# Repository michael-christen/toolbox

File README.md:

# toolbox

My personal monorepo — scripts, libraries, and applications built with Bazel
across Python, C++, and Rust.

**[Documentation](https://michael-christen.github.io/toolbox)** — architecture,
setup, language guides, and command references.

All project code lives under [`tlbox/`](tlbox/) — a language-agnostic namespace
for Python, C++, Rust, and hardware code alike. See
[`docs/development.md`](docs/development.md) to get started, or the
[docs site](https://michael-christen.github.io/toolbox) for everything else.

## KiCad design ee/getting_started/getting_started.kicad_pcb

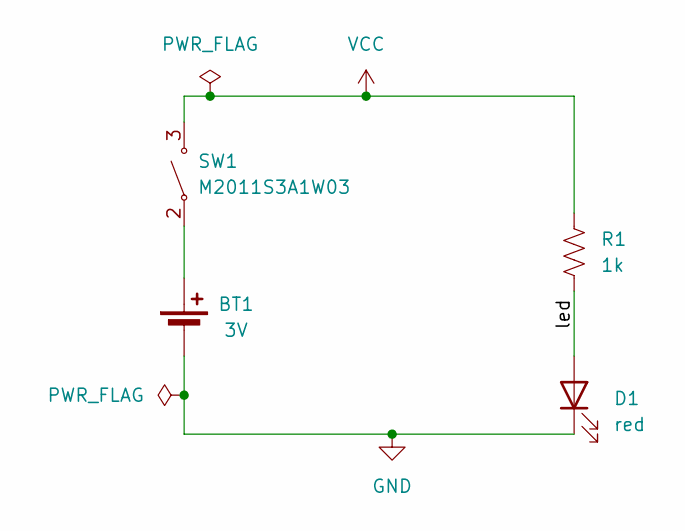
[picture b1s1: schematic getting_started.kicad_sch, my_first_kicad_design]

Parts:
BT1: 3V; BatteryHolder_Keystone_1058_1x2032
D1: red; LED_D5.0mm
R1: 1k; R_Axial_DIN0309_L9.0mm_D3.2mm_P12.70mm_Horizontal
SW1: M2011S3A1W03; Switch_Toggle_SPST_NKK_M2011S3A1x03

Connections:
/led: D1.2 (A), R1.1
GND: BT1.2 (-), D1.1 (K)
unnamed: BT1.1 (+), SW1.2 (A)
VCC: R1.2, SW1.3 (B)

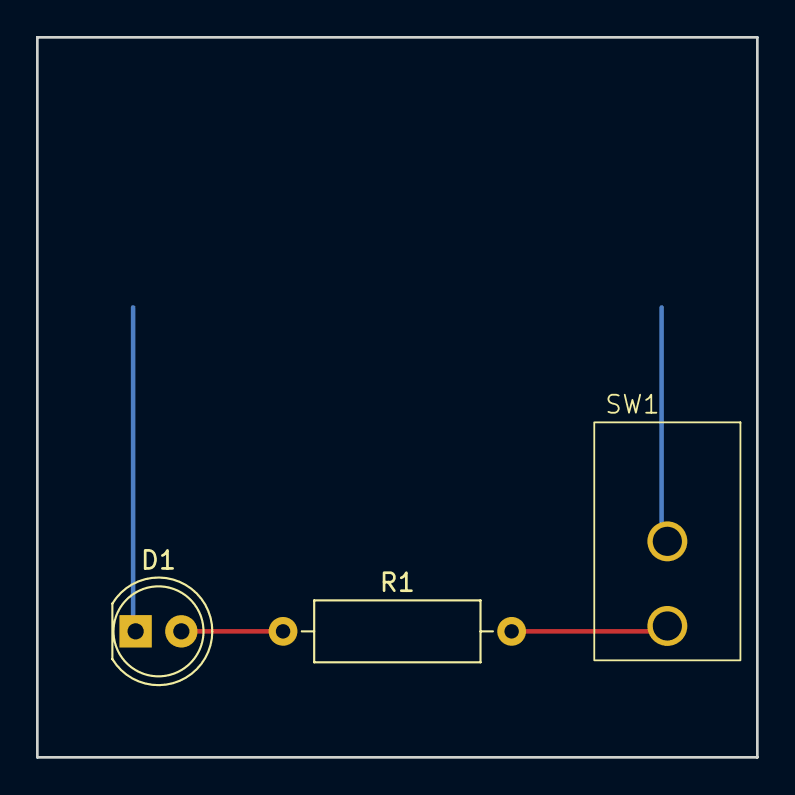
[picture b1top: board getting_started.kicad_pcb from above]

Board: 2 copper layers, 40.0 x 40.0 mm, 4 parts (1 on the bottom side), 4 nets.

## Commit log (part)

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2026-04-02 Fix autoapi by enabling symlink traversal (sphinx-autoapi 3.7.0)
    sphinx-autoapi 3.7.0 introduced autoapi_follow_symlinks with a default
    of False. Bazel sandboxes all source inputs as symlinks, so autoapi
    stopped finding Python files and produced empty API docs.
    https://claude.ai/code/session_01Bn39Pe4L2SSyeQ5M53nFwb
2026-04-02 Apply prettier formatting to markdown files
    https://claude.ai/code/session_013eKgR1WYFB6zvYaCg11DBT
2026-04-02 Fix mypy and query generator failures
    - Use googleapiclient.discovery.Resource type (correct), add
    # type: ignore[attr-defined] for dynamically-generated users() method
    - Add //apps/gmail_analysis:gmail_analysis to packaging/generated.bzl
    https://claude.ai/code/session_01RizaWooJZTLLvezf5z8nag
2026-04-02 Add git LFS documentation to development guide
    https://claude.ai/code/session_01W7Da8VTU6GixAC1fJchVH4
2026-04-03 Lint
2026-04-03 type support
2026-04-03 Bump pyopenssl from 18.0.0 to 26.0.0 in /tlbox/apps/csv-to-sheets
    Bumps [pyopenssl](https://github.com/pyca/pyopenssl) from 18.0.0 to 26.0.0.
    - [Changelog](https://github.com/pyca/pyopenssl/blob/main/CHANGELOG.rst)
    - [Commits](https://github.com/pyca/pyopenssl/compare/18.0.0...26.0.0)
    ---
    updated-dependencies:
    - dependency-name: pyopenssl
2026-04-03 Notes
2026-04-03 Move lint/build/test to BuildBuddy, keep coverage/metrics in GitHub
    BuildBuddy runs in ~1 min vs GitHub's ~10 min, so lint/build/test
    belong there. GitHub CI is now split into two jobs:
    - coverage_and_metrics (required check)
    - build_and_test (non-required, duplicates BuildBuddy for visibility)
    Note: update branch protection to require coverage_and_metrics instead
    of build_and_test.
2026-04-03 Fix missing libncurses5 in coverage_and_metrics job
    Coverage still builds C++ via the llvm toolchain, so libtinfo.so.5
    is still required even without the lint step.
    https://claude.ai/code/session_013eKgR1WYFB6zvYaCg11DBT
2026-04-03 Set permissions
2026-04-03 Bump cryptography from 43.0.1 to 46.0.6 in /tlbox/apps/csv-to-sheets
    Bumps [cryptography](https://github.com/pyca/cryptography) from 43.0.1 to 46.0.6.
    - [Changelog](https://github.com/pyca/cryptography/blob/main/CHANGELOG.rst)
    - [Commits](https://github.com/pyca/cryptography/compare/43.0.1...46.0.6)
    ---
    updated-dependencies:
    - dependency-name: cryptography
2026-04-03 Set these up for bazel
2026-04-03 Format
2026-04-03 Remove legacy apps with their own requirements (#289)
    ## Summary
    Dependabot keeps trying to adjust these, let's just opt into bazel
    - **Remove extra requirements**
    - **Set these up for bazel**
    <!-- What does this PR do and why? -->
    ## Test plan
2026-04-03 Bump pyasn1 from 0.6.2 to 0.6.3
    Bumps [pyasn1](https://github.com/pyasn1/pyasn1) from 0.6.2 to 0.6.3.
    - [Release notes](https://github.com/pyasn1/pyasn1/releases)
    - [Changelog](https://github.com/pyasn1/pyasn1/blob/main/CHANGES.rst)
    - [Commits](https://github.com/pyasn1/pyasn1/compare/v0.6.2...v0.6.3)
    ---
    updated-dependencies:
2026-04-03 Bump requests from 2.32.5 to 2.33.0
    Bumps [requests](https://github.com/psf/requests) from 2.32.5 to 2.33.0.
    - [Release notes](https://github.com/psf/requests/releases)
    - [Changelog](https://github.com/psf/requests/blob/main/HISTORY.md)
    - [Commits](https://github.com/psf/requests/compare/v2.32.5...v2.33.0)
    ---
    updated-dependencies:
2026-04-03 Bump black from 26.1.0 to 26.3.1
    Bumps [black](https://github.com/psf/black) from 26.1.0 to 26.3.1.
    - [Release notes](https://github.com/psf/black/releases)
    - [Changelog](https://github.com/psf/black/blob/main/CHANGES.md)
    - [Commits](https://github.com/psf/black/compare/26.1.0...26.3.1)
    ---
    updated-dependencies:
2026-04-03 Automatically Upgrade Dependencies
2026-04-03 Automatically Upgrade Dependencies (#297)
    Automatically Upgrade Dependencies - by upgrade-dependencies.yml
2026-04-03 Bump setuptools from 70.3.0 to 78.1.1
    Bumps [setuptools](https://github.com/pypa/setuptools) from 70.3.0 to 78.1.1.
    - [Release notes](https://github.com/pypa/setuptools/releases)
    - [Changelog](https://github.com/pypa/setuptools/blob/main/NEWS.rst)
    - [Commits](https://github.com/pypa/setuptools/compare/v70.3.0...v78.1.1)
    ---
    updated-dependencies:
2026-04-03 Adjust setuptools
2026-04-03 deploy: a6e39ded6b5a899a6d9c914769f78cbac9576afd
2026-04-03 Add to actions checkout
2026-04-03 Fix action
2026-04-03 fix actions
2026-04-03 Add trim branches script
2026-04-03 Move gmail analysis (#300)
    ## Summary
    On the tin
    <!-- What does this PR do and why? -->
    ## Test plan
    - CI
2026-04-05 Add lsm6dso and m2t550 drivers under tlbox/hw/drivers/
    Moves the new driver work into the new directory structure introduced
    in #256 (hw_drivers/ -> tlbox/hw/). Updates BUILD to use nanopb
    pattern matching lis3mdl, and fixes include paths throughout.
    Closes #157
    https://claude.ai/code/session_013eKgR1WYFB6zvYaCg11DBT
2026-04-05 Resolve all XXX comments in lsm6dso driver
    - Fix FuncCfgAccess bit positions (bits 6/7 per datasheet, not 0/1)
    - Replace example.cc/.h with a proper lsm6dso_pw_test.cc
    - Stub out sim_lsm6dso.cc with Unimplemented() pending full implementation
    - Remove speculative/WIP XXX comments from .emb and .proto
    - Add *.pdf to .gitattributes as LFS binary
    - Use git grep -I in lint.sh to skip binary files in XXX check
2026-04-06 wrench
2026-04-06 fix pointer
2026-04-06 Add beginning of lsm6dso and m2t550 drivers (#157)
    ## Summary
    - Adds LSM6DSO IMU driver (3-axis gyro + accelerometer) under
    `tlbox/hw/drivers/lsm6dso/`
    - Emboss register definitions (`.emb`)
    - Proto definitions for config/telemetry
    - BUILD updated to nanopb pattern matching `lis3mdl`
2026-04-06 Got an example vpython interaction:
    - robot block
    - viewable wheel rotation
    - reaction to keys pressed
    NEXT: move the robot, make a floor grid, change keypress
    Get all keys at once
    It's alive, just path, no torque
2026-04-06 More lint :(
2026-04-06 cleanup
2026-04-06 Create local vpython
2026-04-06 Update requirements
2026-04-06 Remove
2026-04-06 Enable remote_cache_compression
2026-04-06 Fix self-edge
2026-04-06 A bunch of raw notes after reading bazel docs (#80)
2026-04-07 Update aspect rules_py (#304)
    On the tin, see https://github.com/aspect-build/rules_py/pull/840
    Should bring in bin scripts, though didn't get evidence of that
2026-04-07 deploy: 5629891ece6f42bcb188f826ac68bae6bd585cb1
2026-04-07 update kicad v10
2026-04-07 Wild
2026-04-08 Say -y
2026-04-08 Bump cryptography from 46.0.6 to 46.0.7
    Bumps [cryptography](https://github.com/pyca/cryptography) from 46.0.6 to 46.0.7.
    - [Changelog](https://github.com/pyca/cryptography/blob/main/CHANGELOG.rst)
    - [Commits](https://github.com/pyca/cryptography/compare/46.0.6...46.0.7)
    ---
    updated-dependencies:
    - dependency-name: cryptography
2026-04-09 Design doc
2026-04-09 Add some dates
2026-04-11 Update gazelle
2026-04-13 New schematic
2026-04-13 Add links and fix after lint
2026-04-13 Revert "Defer KiCad Bazel rules and hardware docs to stacked PR"
    This reverts commit 9ad1201c066043e5dfe772eac2c05005862cd8ec.
2026-04-13 deploy: af9f19203feb895afe8c03bcc65f4dfa55a2b86a
2026-04-13 Fix #319: generate KiCad hardware artifacts in docs workflow
    - Add workflow_dispatch trigger with optional publish input so docs can
    be built and inspected without automatically pushing to GitHub Pages
    - Install kicad-cli (via KiCad 7 PPA) to generate PDFs from KiCad
    schematic and PCB files for sbr_pcb_v1 and getting_started projects
    - Collect Sphinx HTML output and hardware PDFs together into docs_site/
    staging directory before upload
2026-04-14 Bump rand from 0.8.5 to 0.9.3 in /nobazel/learn_rust/guessing_game
    Bumps [rand](https://github.com/rust-random/rand) from 0.8.5 to 0.9.3.
    - [Release notes](https://github.com/rust-random/rand/releases)
    - [Changelog](https://github.com/rust-random/rand/blob/0.9.3/CHANGELOG.md)
    - [Commits](https://github.com/rust-random/rand/compare/0.8.5...0.9.3)
    ---
    updated-dependencies:
2026-04-14 Fix #319: add workflow_dispatch trigger to docs workflow
    Allows manually triggering the docs build without a push to master.
    The publish input (default true) controls whether the result is
    pushed to GitHub Pages, enabling preview builds without publishing.
    https://claude.ai/code/session_012AJErFw2FiX9N3B38niFaT
2026-04-14 Bump pytest from 9.0.2 to 9.0.3 (#321)
    Bumps [pytest](https://github.com/pytest-dev/pytest) from 9.0.2 to
    9.0.3.
    <details>
    <summary>Release notes</summary>
    <p><em>Sourced from <a
    href="https://github.com/pytest-dev/pytest/releases">pytest's
2026-04-23 Bump rand from 0.8.5 to 0.8.6 in /nobazel/learn_rust/guessing_game
    Bumps [rand](https://github.com/rust-random/rand) from 0.8.5 to 0.8.6.
    - [Release notes](https://github.com/rust-random/rand/releases)
    - [Changelog](https://github.com/rust-random/rand/blob/0.8.6/CHANGELOG.md)
    - [Commits](https://github.com/rust-random/rand/compare/0.8.5...0.8.6)
    ---
    updated-dependencies:
2026-04-27 Add OCI/ORAS firmware artifact management experiment
    Evaluates using OCI registries + the oras Python SDK to push/pull
    firmware blobs with provenance metadata (version, target, sha256,
    build config) as OCI manifest annotations. Digest verification is
    automatic via the content-addressable store.
    To run: start a local registry with `docker run -d -p 5000:5000 registry:2`
    then `bazel run //examples/oras:oras_example`.
2026-04-27 Add rdl, README, requirements
2026-04-27 version info
2026-04-30 Bump jupyterlab from 4.5.6 to 4.5.7
    ---
    updated-dependencies:
    - dependency-name: jupyterlab
    dependency-version: 4.5.7
    dependency-type: direct:production
    ...
2026-05-06 Bump pip from 26.0.1 to 26.1
    Bumps [pip](https://github.com/pypa/pip) from 26.0.1 to 26.1.
    - [Changelog](https://github.com/pypa/pip/blob/main/NEWS.rst)
    - [Commits](https://github.com/pypa/pip/compare/26.0.1...26.1)
    ---
    updated-dependencies:
    - dependency-name: pip
2026-05-11 Bump urllib3 from 2.6.3 to 2.7.0
    Bumps [urllib3](https://github.com/urllib3/urllib3) from 2.6.3 to 2.7.0.
    - [Release notes](https://github.com/urllib3/urllib3/releases)
    - [Changelog](https://github.com/urllib3/urllib3/blob/main/CHANGES.rst)
    - [Commits](https://github.com/urllib3/urllib3/compare/2.6.3...2.7.0)
    ---
    updated-dependencies:
2026-05-16 Notes on tools/affected_targets.sh WIP
2026-06-03 Bump aiohttp from 3.13.5 to 3.14.0
    ---
    updated-dependencies:
    - dependency-name: aiohttp
    dependency-version: 3.14.0
    dependency-type: direct:production
    ...
2026-06-12 Bump tornado from 6.4.2 to 6.5.6
    Bumps [tornado](https://github.com/tornadoweb/tornado) from 6.4.2 to 6.5.6.
    - [Changelog](https://github.com/tornadoweb/tornado/blob/master/docs/releases.rst)
    - [Commits](https://github.com/tornadoweb/tornado/compare/v6.4.2...v6.5.6)
    ---
    updated-dependencies:
    - dependency-name: tornado
2026-06-17 Bump aiohttp from 3.13.5 to 3.14.1
    ---
    updated-dependencies:
    - dependency-name: aiohttp
    dependency-version: 3.14.1
    dependency-type: direct:production
    ...
2026-06-20 Bump bleach from 6.3.0 to 6.4.0
    Bumps [bleach](https://github.com/mozilla/bleach) from 6.3.0 to 6.4.0.
    - [Changelog](https://github.com/mozilla/bleach/blob/main/CHANGES)
    - [Commits](https://github.com/mozilla/bleach/compare/v6.3.0...v6.4.0)
    ---
    updated-dependencies:
    - dependency-name: bleach
